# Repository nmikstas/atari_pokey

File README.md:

# atari_pokey
Recreation of the Atari POKEY chip (work in progress)

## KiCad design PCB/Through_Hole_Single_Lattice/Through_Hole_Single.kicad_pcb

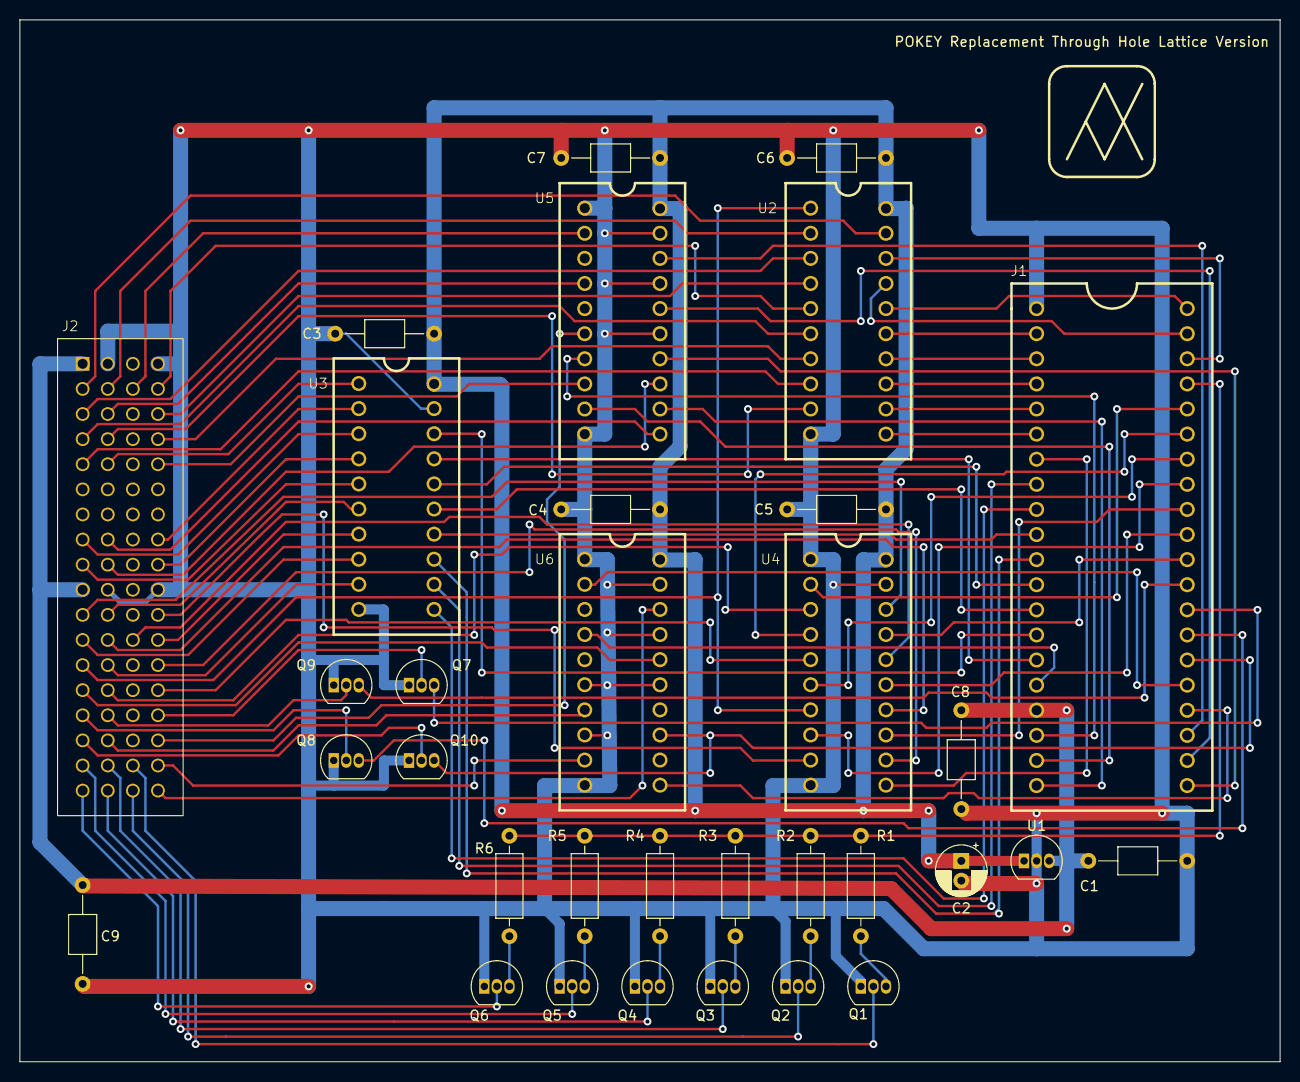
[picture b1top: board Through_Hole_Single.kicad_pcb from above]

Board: 2 copper layers, 127.5 x 105.4 mm, 33 parts (0 on the bottom side), 93 nets.

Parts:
C1, C3, C4, C5, C6, C7, C8, C9: .1uf; C_Axial_L3.8mm_D2.6mm_P10.00mm_Horizontal
C2: 10uf; CP_Radial_D5.0mm_P2.00mm
J1: 2x20_Conn; Con_2X20
J2: Proto-72Pin
Q1, Q2, Q3, Q4, Q5, Q6, Q7, Q8, Q9, Q10: TN2106; TO-92_Inline
R1: 825 1%; R_Axial_DIN0207_L6.3mm_D2.5mm_P10.16mm_Horizontal
R2: 1.65K 1%; R_Axial_DIN0207_L6.3mm_D2.5mm_P10.16mm_Horizontal
R3: 3.3K 1%; R_Axial_DIN0207_L6.3mm_D2.5mm_P10.16mm_Horizontal
R4: 7.68K 1%; R_Axial_DIN0207_L6.3mm_D2.5mm_P10.16mm_Horizontal
R5: 24K 1%; R_Axial_DIN0207_L6.3mm_D2.5mm_P10.16mm_Horizontal
R6: 75K 1%; R_Axial_DIN0207_L6.3mm_D2.5mm_P10.16mm_Horizontal
U1: L78L05_TO92; TO-92_Inline
U2, U3, U4, U5, U6: DIP_20

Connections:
+3.3V: C2.1, C3.1, C4.1, C5.1, C6.1, C7.1, U1.1 (VO), U2.20 (VCC), U3.20 (VCC), U4.20 (VCC), U5.20 (VCC), U6.20 (VCC)
+5V: C1.1, C8.1, C9.1, J1.17 (+5V), J2.1 (5V1), J2.37 (5V2), U1.3 (VI)
A0: J1.36 (A0), U4.2 (1A1)
A1: J1.35 (A1), U4.4 (1A2)
A2: J1.34 (A2), U4.6 (1A3)
A3: J1.33 (A3), U4.8 (1A4)
AUDIO: J1.37 (AUDIO), R1.1, R2.1, R3.1, R4.1, R5.1, R6.1
BCLK: J1.26 (BCLK), Q10.3 (D), U6.13 (2A2)
CS1: J1.31 (CS1), U4.15 (2A3)
D0: J1.38 (D0), U2.18 (B0)
D1: J1.39 (D1), U2.17 (B1)
D2: J1.40 (D2), U2.16 (B2)
D3: J1.2 (D3), U2.15 (B3)
D4: J1.3 (D4), U2.14 (B4)
D5: J1.4 (D5), U2.13 (B5)
D6: J1.5 (D6), U2.12 (B6)
D7: J1.6 (D7), U2.11 (B7)
GND: C1.2, C2.2, C3.2, C4.2, C5.2, C6.2, C7.2, C8.2, C9.2, J1.1 (GND), J2.2 (G1), J2.4 (G2), J2.38 (G3), J2.40 (G4), Q1.1 (S), Q2.1 (S), Q3.1 (S), Q4.1 (S), Q5.1 (S), Q6.1 (S), Q7.1 (S), Q8.1 (S), Q9.1 (S), Q10.1 (S), U1.2 (GND), U2.10 (GND), U3.10 (GND), U3.19 (CE), U4.1 (1~OE), U4.10 (GND), U4.19 (2~OE), U5.1 (1~OE), U5.10 (GND), U5.15 (2A3), U5.17 (2A4), U5.19 (2~OE), U6.1 (1~OE), U6.6 (1A3), U6.8 (1A4), U6.10 (GND), U6.15 (2A3), U6.17 (2A4), U6.19 (2~OE)
unnamed: Q1.3 (D), R1.2
unnamed: Q2.3 (D), R2.2
unnamed: Q3.3 (D), R3.2
unnamed: Q4.3 (D), R4.2
unnamed: Q5.3 (D), R5.2
unnamed: Q6.3 (D), R6.2
OCLK: J1.27 (OCLK), Q8.3 (D)
P0: J1.14 (P0), U3.18 (B0)
P1: J1.15 (P1), U3.17 (B1)
P2: J1.12 (P2), U3.16 (B2)
P3: J1.13 (P3), U3.15 (B3)
P4: J1.10 (P4), U3.14 (B4)
P5: J1.11 (P5), U3.13 (B5)
P6: J1.8 (P6), U3.12 (B6)
P7: J1.9 (P7), U3.11 (B7)
PHI2: J1.7 (PHI2), U4.11 (2A1)
R/W: J1.32 (R/W), U4.13 (2A2)
SID: J1.24 (SID), U6.11 (2A1)
SOD: J1.28 (SOD), Q7.3 (D)
_A0: J2.41 (B48), U4.18 (1Y1)
_A1: J2.47 (B6), U4.16 (1Y2)
_A2: J2.46 (B46), U4.14 (1Y3)
_A3: J2.52 (B8), U4.12 (1Y4)
_AUDIO0: J2.69 (B27), Q6.2 (G)
_AUDIO1: J2.65 (B30), Q5.2 (G)
_AUDIO2: J2.70 (B28), Q4.2 (G)
_AUDIO3: J2.66 (B31), Q3.2 (G)
_AUDIO4: J2.71 (B24), Q2.2 (G)
_AUDIO5: J2.67 (B21), Q1.2 (G)
_BCLKI: J2.62 (B34), U6.7 (2Y2)
_BCLKO: J2.61 (B33), Q10.2 (G)
_CS1: J2.56 (B11), U4.5 (2Y3)
_D0: J2.6 (A49), U2.2 (A0)
_D1: J2.9 (A45), U2.3 (A1)
_D2: J2.12 (A5), U2.4 (A2)
_D3: J2.8 (A2), U2.5 (A3)
_D4: J2.13 (A42), U2.6 (A4)
_D5: J2.16 (A8), U2.7 (A5)
_D6: J2.17 (A39), U2.8 (A6)
_D7: J2.14 (A43), U2.9 (A7)
_DUMP: J2.18 (A40), U3.1 (A->B)
_OCLK: J2.57 (B36), Q8.2 (G)
_P0: J2.32 (A20), U3.2 (A0)
_P1: J2.29 (A30), U3.3 (A1)
_P2: J2.36 (A23), U3.4 (A2)
_P3: J2.33 (A27), U3.5 (A3)
_P4: J2.42 (B49), U3.6 (A4)
_P5: J2.48 (B5), U3.7 (A5)
_P6: J2.45 (B45), U3.8 (A6)
_P7: J2.50 (B43), U3.9 (A7)
_PHI2: J2.44 (B2), U4.9 (2Y1)
_R/W: J2.49 (B42), U2.1 (A->B), U4.7 (2Y2)
_SID: J2.68 (B20), U6.9 (2Y1)
_SOD: J2.60 (B14), Q7.2 (G)
_~CS0: J2.54 (B40), U4.3 (2Y4)
_~IRQ: J2.58 (B37), Q9.2 (G)
_~K0: J2.7 (A3), U5.2 (1A1)
_~K1: J2.10 (A46), U5.4 (1A2)
_~K2: J2.64 (B17), U5.6 (1A3)
_~K3: J2.20 (A11), U5.8 (1A4)
_~K4: J2.30 (A31), U5.11 (2A1)
_~K5: J2.34 (A28), U5.13 (2A2)
_~KR1: J2.72 (B23), U6.18 (1Y1)
_~KR2: J2.53 (B39), U6.16 (1Y2)
~CS0: J1.30 (~CS0), U4.17 (2A4)
~IRQ: J1.29 (~IRQ), Q9.3 (D)
~K0: J1.23 (~K0), U5.18 (1Y1)
~K1: J1.22 (~K1), U5.16 (1Y2)
~K2: J1.21 (~K2), U5.14 (1Y3)
~K3: J1.20 (~K3), U5.12 (1Y4)
~K4: J1.19 (~K4), U5.9 (2Y1)
~K5: J1.18 (~K5), U5.7 (2Y2)
~KR1: J1.25 (~KR1), U6.2 (1A1)
~KR2: J1.16 (~KR2), U6.4 (1A2)
~_EN: J2.5 (A48), U2.19 (CE)

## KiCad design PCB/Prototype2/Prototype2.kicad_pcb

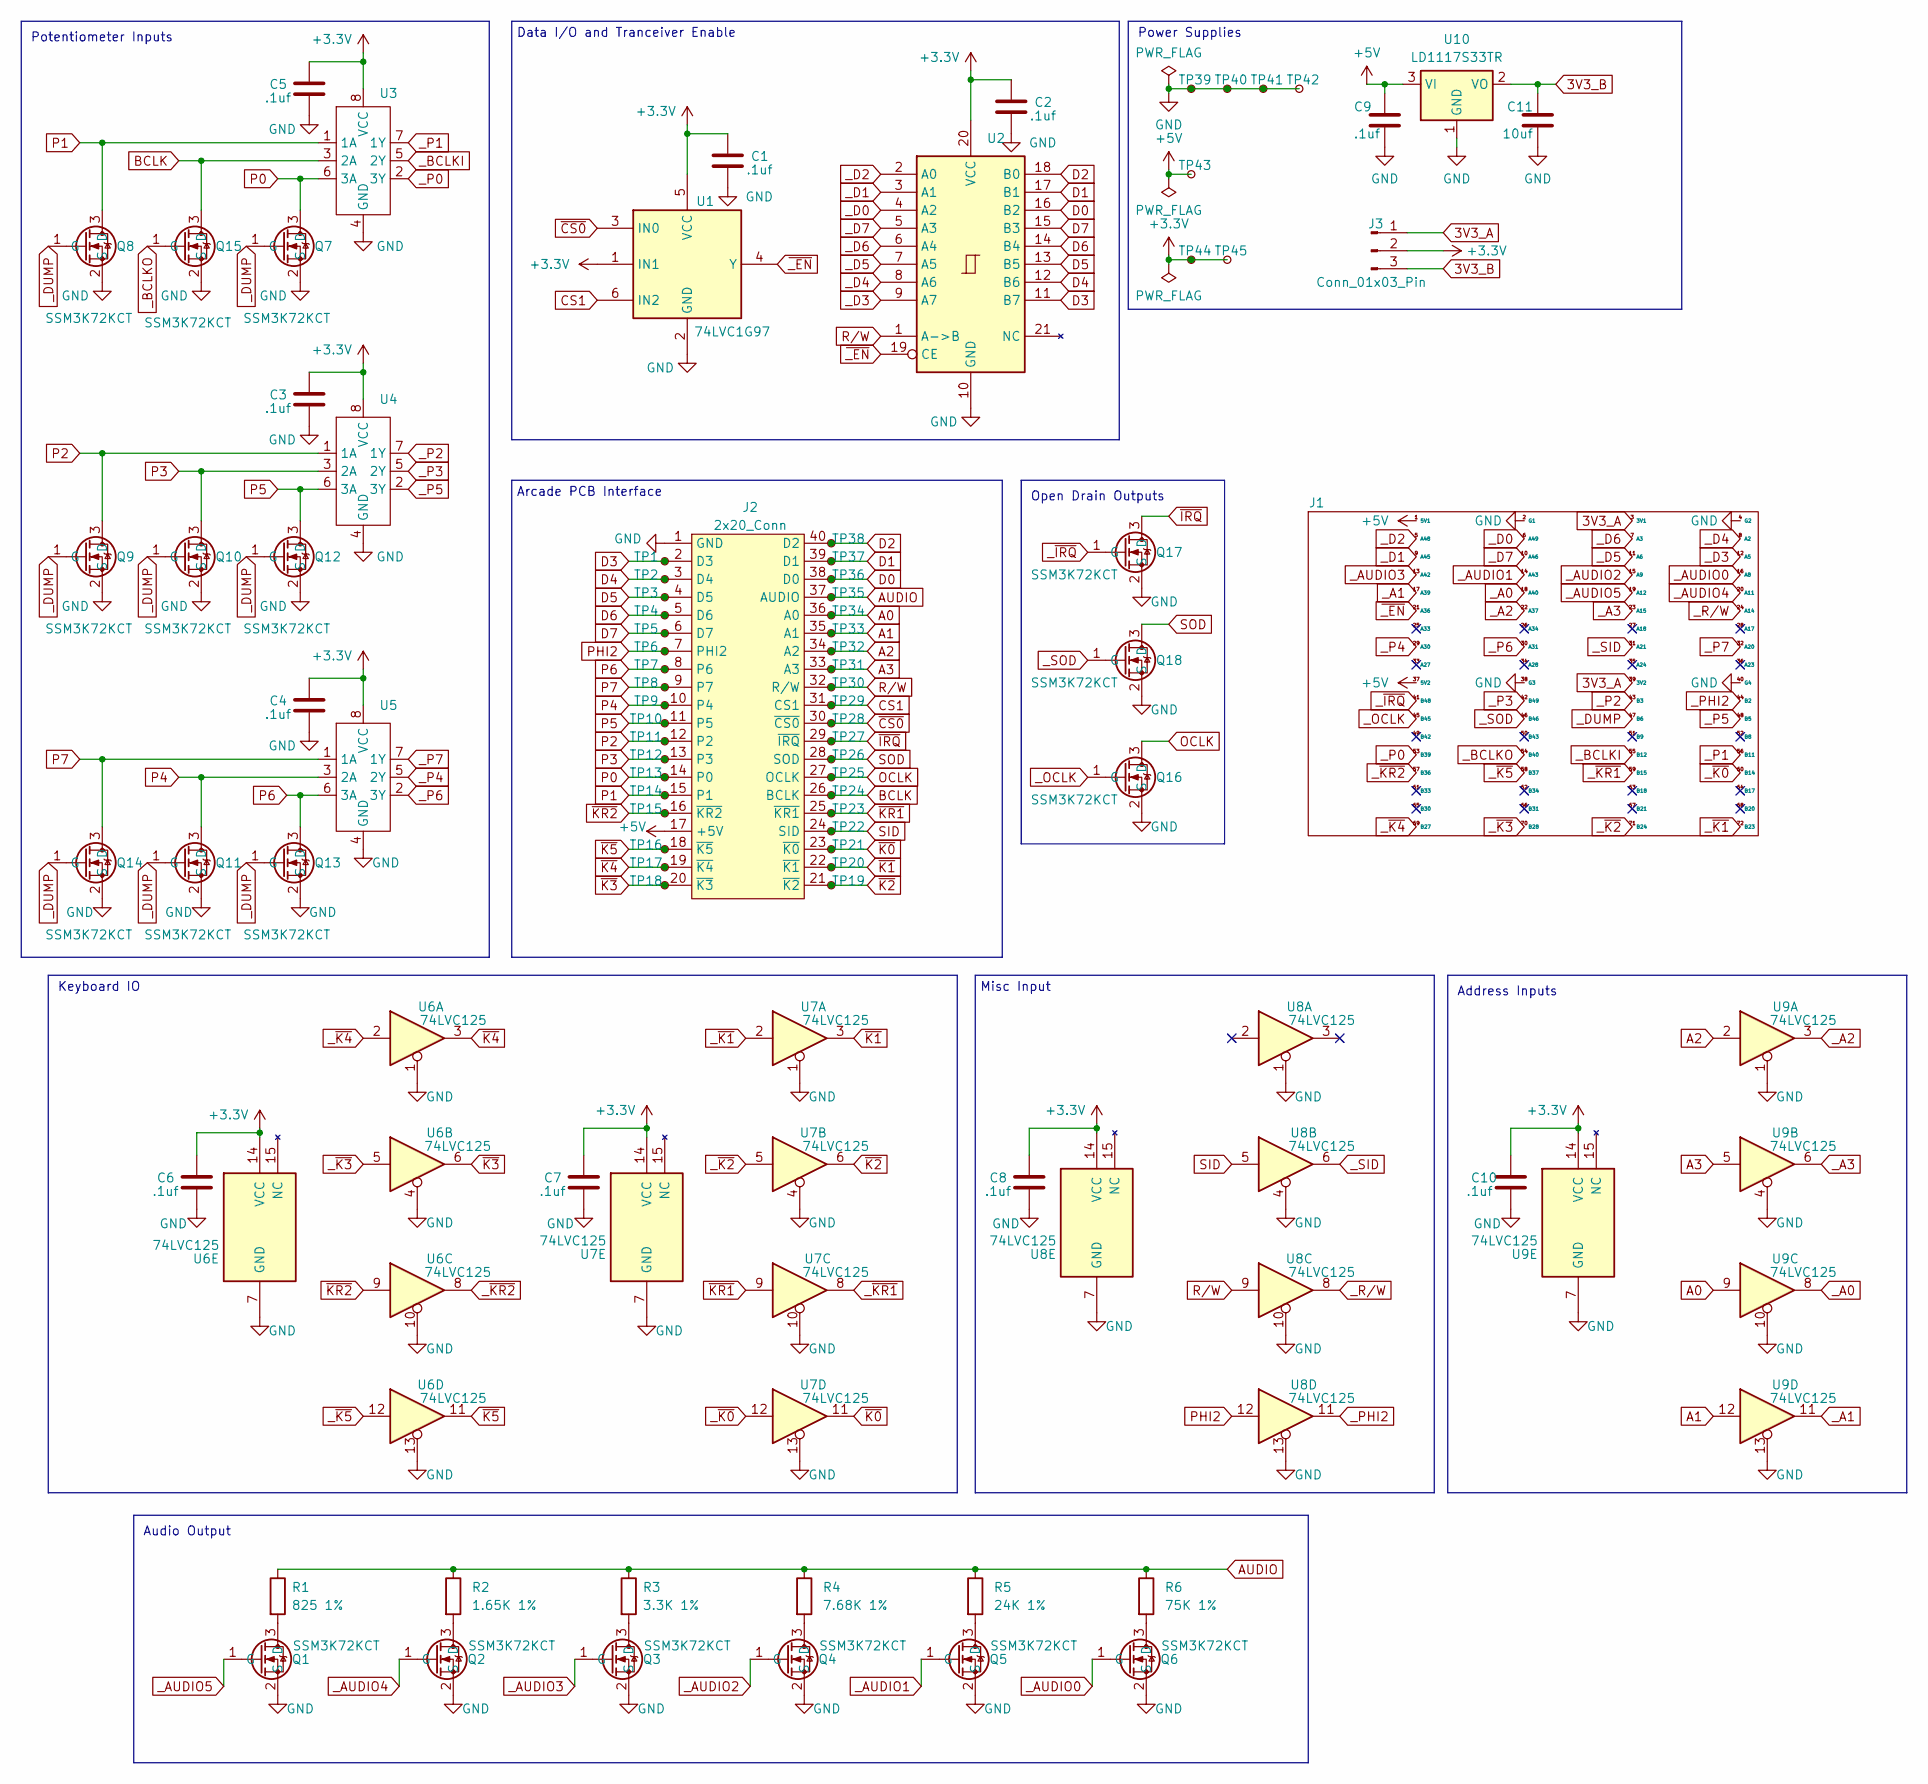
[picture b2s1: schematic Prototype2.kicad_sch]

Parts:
C1, C2, C3, C4, C5, C6, C7, C8, C9, C10: .1uf; C_0201_0603Metric
C11: 10uf; C_0805_2012Metric
J1: Proto-72Pin
J2: 2x20_Conn; Con_2X20
J3: Conn_01x03_Pin; PinSocket_1x03_P2.54mm_Vertical
Q1, Q2, Q3, Q4, Q5, Q6, Q7, Q8, Q9, Q10, Q11, Q12, Q13, Q14, Q15, Q16, Q17, Q18: SSM3K72KCT; CST3_TOS
R1: 825 1%; R_0402_1005Metric
R2: 1.65K 1%; R_0201_0603Metric
R3: 3.3K 1%; R_0201_0603Metric
R4: 7.68K 1%; R_0201_0603Metric
R5: 24K 1%; R_0201_0603Metric
R6: 75K 1%; R_0201_0603Metric
TP1, TP2, TP3, TP4, TP5, TP6, TP7, TP8, TP9, TP10, TP11, TP12, TP13, TP14, TP15, TP16, TP17, TP18, TP19, TP20, TP21, TP22, TP23, TP24, TP25, TP26, TP27, TP28, TP29, TP30, TP31, TP32, TP33, TP34, TP35, TP36, TP37, TP38, TP39, TP40, TP41, TP42, TP43, TP44, TP45: TP
U1: 74LVC1G97; DRY6
U2: VQFN20_RKS_TEX
U3, U4, U5: XSON8
U6, U7, U8, U9: 74LVC125; DHVQFN14_SOT762-1_NEX
U10: LD1117S33TR; Reg

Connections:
3V3_A: J1.3 (3V1), J1.39 (3V2), J3.1
3V3_B: C11.1, J3.3, U10.2 (VO)
+3.3V: C1.1, C2.1, C3.1, C4.1, C5.1, C6.1, C7.1, C8.1, C10.1, J3.2, TP44.1, TP45.1, U1.1 (IN1), U1.5 (VCC), U2.20 (VCC), U3.8 (VCC), U4.8 (VCC), U5.8 (VCC), U6.14 (VCC), U7.14 (VCC), U8.14 (VCC), U9.14 (VCC)
+5V: C9.1, J1.1 (5V1), J1.37 (5V2), J2.17 (+5V), TP43.1, U10.3 (VI)
A0: J2.36 (A0), TP34.1, U9.9
A1: J2.35 (A1), TP33.1, U9.12
A2: J2.34 (A2), TP32.1, U9.2
A3: J2.33 (A3), TP31.1, U9.5
AUDIO: J2.37 (AUDIO), R1.1, R2.1, R3.1, R4.1, R5.1, R6.1, TP35.1
BCLK: J2.26 (BCLK), Q15.3 (D), TP24.1, U3.3 (2A)
CS1: J2.31 (CS1), TP29.1, U1.6 (IN2)
D0: J2.38 (D0), TP36.1, U2.16 (B2)
D1: J2.39 (D1), TP37.1, U2.17 (B1)
D2: J2.40 (D2), TP38.1, U2.18 (B0)
D3: J2.2 (D3), TP1.1, U2.11 (B7)
D4: J2.3 (D4), TP2.1, U2.12 (B6)
D5: J2.4 (D5), TP3.1, U2.13 (B5)
D6: J2.5 (D6), TP4.1, U2.14 (B4)
D7: J2.6 (D7), TP5.1, U2.15 (B3)
GND: C1.2, C2.2, C3.2, C4.2, C5.2, C6.2, C7.2, C8.2, C9.2, C10.2, C11.2, J1.2 (G1), J1.4 (G2), J1.38 (G3), J1.40 (G4), J2.1 (GND), Q1.2 (S), Q2.2 (S), Q3.2 (S), Q4.2 (S), Q5.2 (S), Q6.2 (S), Q7.2 (S), Q8.2 (S), Q9.2 (S), Q10.2 (S), Q11.2 (S), Q12.2 (S), Q13.2 (S), Q14.2 (S), Q15.2 (S), Q16.2 (S), Q17.2 (S), Q18.2 (S), TP39.1, TP40.1, TP41.1, TP42.1, U1.2 (GND), U2.10 (GND), U3.4 (GND), U4.4 (GND), U5.4 (GND), U6.1, U6.4, U6.7 (GND), U6.10, U6.13, U7.1, U7.4, U7.7 (GND), U7.10, U7.13, U8.1, U8.4, U8.7 (GND), U8.10, U8.13, U9.1, U9.4, U9.7 (GND), U9.10, U9.13, U10.1 (GND)
unnamed: Q1.3 (D), R1.2
unnamed: Q2.3 (D), R2.2
unnamed: Q3.3 (D), R3.2
unnamed: Q4.3 (D), R4.2
unnamed: Q5.3 (D), R5.2
unnamed: Q6.3 (D), R6.2
OCLK: J2.27 (OCLK), Q16.3 (D), TP25.1
P0: J2.14 (P0), Q7.3 (D), TP13.1, U3.6 (3A)
P1: J2.15 (P1), Q8.3 (D), TP14.1, U3.1 (1A)
P2: J2.12 (P2), Q9.3 (D), TP11.1, U4.1 (1A)
P3: J2.13 (P3), Q10.3 (D), TP12.1, U4.3 (2A)
P4: J2.10 (P4), Q11.3 (D), TP9.1, U5.3 (2A)
P5: J2.11 (P5), Q12.3 (D), TP10.1, U4.6 (3A)
P6: J2.8 (P6), Q13.3 (D), TP7.1, U5.6 (3A)
P7: J2.9 (P7), Q14.3 (D), TP8.1, U5.1 (1A)
PHI2: J2.7 (PHI2), TP6.1, U8.12
R/W: J2.32 (R/W), TP30.1, U2.1 (A->B), U8.9
SID: J2.24 (SID), TP22.1, U8.5
SOD: J2.28 (SOD), Q18.3 (D), TP26.1
_A0: J1.18 (A40), U9.8
_A1: J1.17 (A39), U9.11
_A2: J1.22 (A37), U9.3
_A3: J1.23 (A15), U9.6
_AUDIO0: J1.16 (A8), Q6.1 (G)
_AUDIO1: J1.14 (A43), Q5.1 (G)
_AUDIO2: J1.15 (A9), Q4.1 (G)
_AUDIO3: J1.13 (A42), Q3.1 (G)
_AUDIO4: J1.20 (A11), Q2.1 (G)
_AUDIO5: J1.19 (A12), Q1.1 (G)
_BCLKI: J1.55 (B12), U3.5 (2Y)
_BCLKO: J1.54 (B40), Q15.1 (G)
_D0: J1.6 (A49), U2.4 (A2)
_D1: J1.9 (A45), U2.3 (A1)
_D2: J1.5 (A48), U2.2 (A0)
_D3: J1.12 (A5), U2.9 (A7)
_D4: J1.8 (A2), U2.8 (A6)
_D5: J1.11 (A6), U2.7 (A5)
_D6: J1.7 (A3), U2.6 (A4)
_D7: J1.10 (A46), U2.5 (A3)
_DUMP: J1.47 (B6), Q7.1 (G), Q8.1 (G), Q9.1 (G), Q10.1 (G), Q11.1 (G), Q12.1 (G), Q13.1 (G), Q14.1 (G)
_OCLK: J1.45 (B45), Q16.1 (G)
_P0: J1.53 (B39), U3.2 (3Y)
_P1: J1.56 (B11), U3.7 (1Y)
_P2: J1.43 (B3), U4.7 (1Y)
_P3: J1.42 (B49), U4.5 (2Y)
_P4: J1.29 (A30), U5.5 (2Y)
_P5: J1.48 (B5), U4.2 (3Y)
_P6: J1.30 (A31), U5.2 (3Y)
_P7: J1.32 (A20), U5.7 (1Y)
_PHI2: J1.44 (B2), U8.11
_R/W: J1.24 (A14), U8.8
_SID: J1.31 (A21), U8.6
_SOD: J1.46 (B46), Q18.1 (G)
_~IRQ: J1.41 (B48), Q17.1 (G)
_~K0: J1.60 (B14), U7.12
_~K1: J1.72 (B23), U7.2
_~K2: J1.71 (B24), U7.5
_~K3: J1.70 (B28), U6.5
_~K4: J1.69 (B27), U6.2
_~K5: J1.58 (B37), U6.12
_~KR1: J1.59 (B15), U7.8
_~KR2: J1.57 (B36), U6.8
~CS0: J2.30 (~CS0), TP28.1, U1.3 (IN0)
~IRQ: J2.29 (~IRQ), Q17.3 (D), TP27.1
~K0: J2.23 (~K0), TP21.1, U7.11
~K1: J2.22 (~K1), TP20.1, U7.3
~K2: J2.21 (~K2), TP19.1, U7.6
~K3: J2.20 (~K3), TP18.1, U6.6
~K4: J2.19 (~K4), TP17.1, U6.3
~K5: J2.18 (~K5), TP16.1, U6.11
~KR1: J2.25 (~KR1), TP23.1, U7.9
~KR2: J2.16 (~KR2), TP15.1, U6.9
~_EN: J1.21 (A36), U1.4 (Y), U2.19 (CE)

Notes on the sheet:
Keyboard IO
Power Supplies
Potentiometer Inputs
Arcade PCB Interface
Data I/O and Tranceiver Enable
Audio Output
Address Inputs
Misc Input
Open Drain Outputs

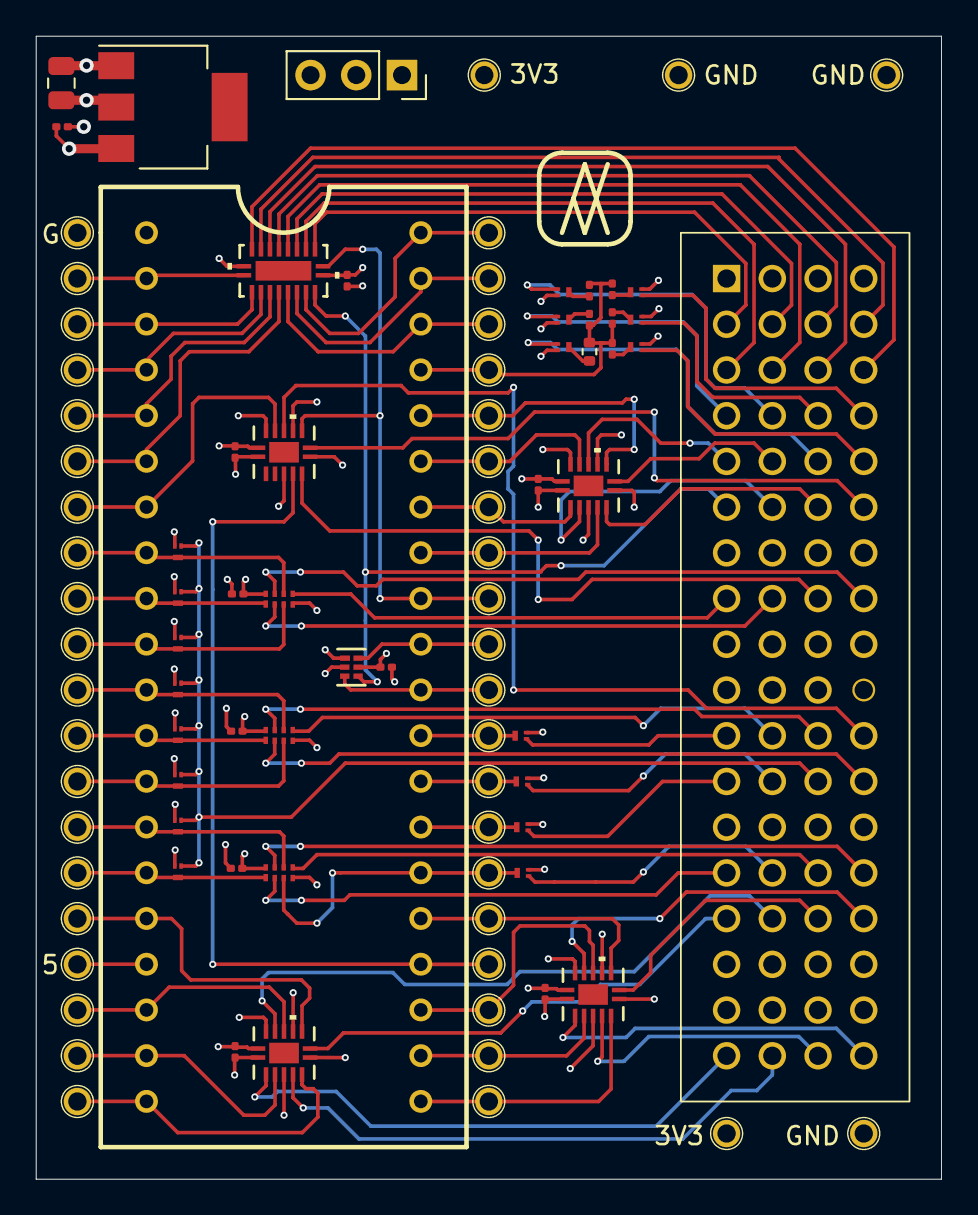
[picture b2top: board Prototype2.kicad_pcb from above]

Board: 4 copper layers, 50.3 x 63.5 mm, 93 parts (0 on the bottom side), 93 nets.

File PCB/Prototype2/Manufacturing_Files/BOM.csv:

Quantity           Component                                                   Value               Part#
10                 C1 C2 C3 C4 C5 C6 C7 C8 C9 C10                              .1uf                Digikey 1292-1161-1-ND or equivalent
1                  C11                                                         10uf                Digikey 1276-1096-1-ND or equivalent
1                  J1                                                          4X18_Conn           N/A
1                  J2                                                          2x20_Conn           N/A
1                  J3                                                          1x03_Pin            N/A

18                 Q1  Q2  Q3  Q4  Q5  Q6  Q7  Q8  Q9  Q10                     SSM3K72KCT          Digikey SSM3K72KCTL3FCT-ND or equivalent
                   Q11 Q12 Q13 Q14 Q15 Q16 Q17 Q18

1                  R1                                                          825 1%              Digikey YAG3242CT-ND or equivalent
1                  R2                                                          1.65K 1%            Digikey YAG2486CT-ND or equivalent
1                  R3                                                          3.3K 1%             Digikey YAG2285CT-ND or equivalent
1                  R4                                                          7.68K 1%            Digikey YAG2806CT-ND or equivalent
1                  R5                                                          24K 1%              Digikey YAG2336CT-ND or equivalent
1                  R6                                                          75K 1%              Digikey YAG2795CT-ND or equivalent

46                 TP1  TP2  TP3  TP4  TP5  TP6  TP7  TP8  TP9  TP10           Test point          N/A
                   TP11 TP12 TP13 TP14 TP15 TP16 TP17 TP18 TP19 TP20
                   TP21 TP22 TP23 TP24 TP25 TP26 TP27 TP28 TP29 TP30
                   TP31 TP32 TP33 TP34 TP35 TP36 TP37 TP38 TP39 TP40
                   TP41 TP42 TP43 TP44 TP45 TP46

1                  U1                                                          74LVC1G97           296-29874-1-ND or equivalent
1                  U2                                                          74LVC245            1727-3495-1-ND or equivalent
3                  U3 U4 U5                                                    74LVC3G14           1727-7042-1-ND or equivalent
4                  U6 U7 U8 U9                                                 74LVC125            1727-3481-1-ND or equivalent
1                  U10                                                         LD1117S33TR         497-1242-1-ND  or equivalent

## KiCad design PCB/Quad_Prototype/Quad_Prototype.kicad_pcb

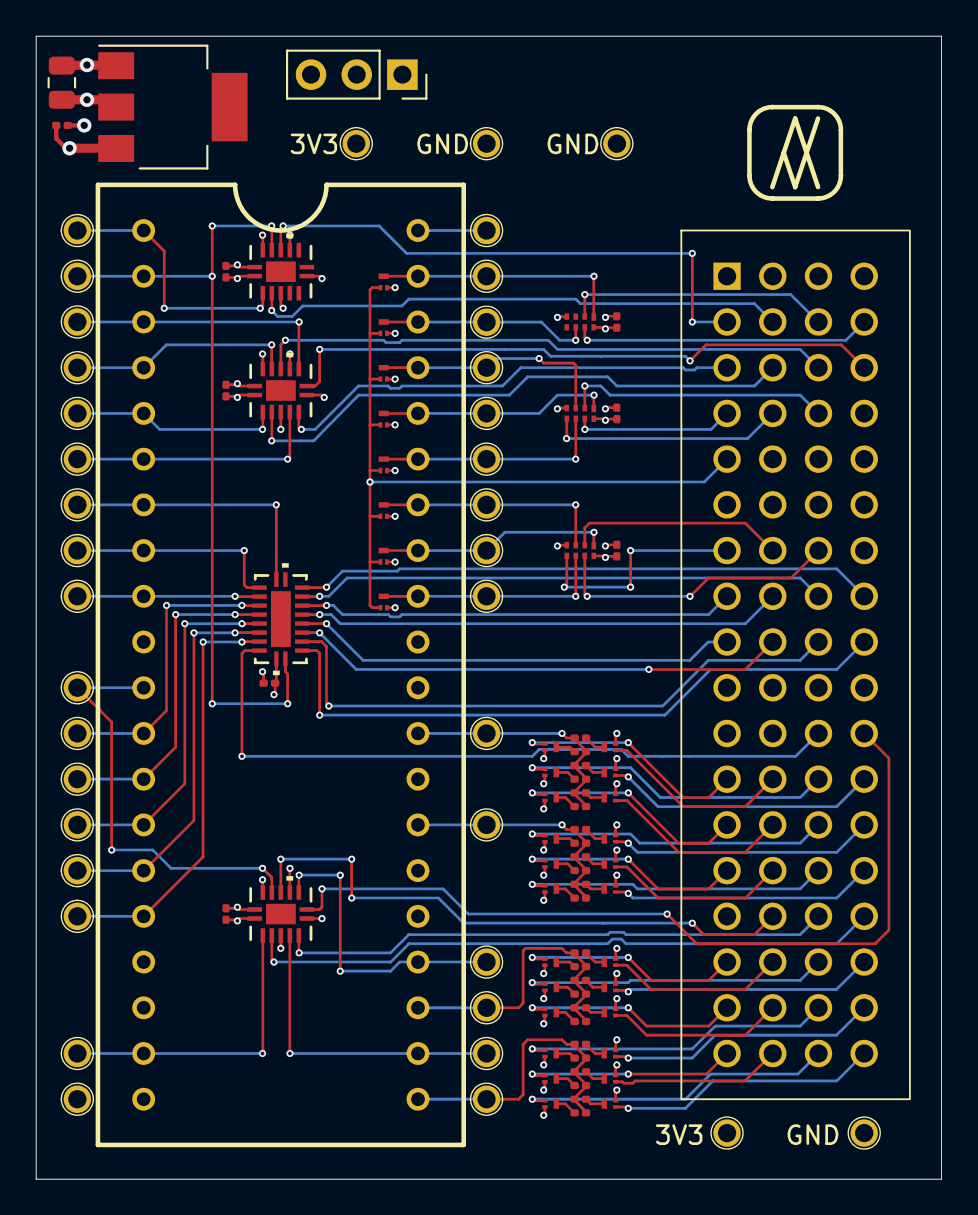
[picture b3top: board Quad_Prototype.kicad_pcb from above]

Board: 4 copper layers, 50.3 x 63.5 mm, 113 parts (0 on the bottom side), 111 nets.

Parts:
C1, C3, C4, C5, C6, C7, C8, C9: .1uf; C_0201_0603Metric
C2: 10uf; C_0805_2012Metric
J1: Con_2X20
J2: Proto-72Pin
J3: Conn_01x03_Pin; PinSocket_1x03_P2.54mm_Vertical
Q1, Q2, Q3, Q4, Q5, Q6, Q7, Q8, Q9, Q10, Q11, Q12, Q13, Q14, Q15, Q16, Q17, Q18, Q19, Q20, Q21, Q22, Q23, Q24, Q25, Q26, Q27, Q29, Q30, Q31, Q32, Q33: SSM3K72KCT; CST3_TOS
R1, R7, R13, R19: 825 1%; R_0201_0603Metric
R2, R8, R14, R20: 1.65K 1%; R_0201_0603Metric
R3, R9, R15, R21: 3.3K 1%; R_0201_0603Metric
R4, R10, R16, R22: 7.68K 1%; R_0201_0603Metric
R5, R11, R17, R23: 24K 1%; R_0201_0603Metric
R6, R12, R18, R24: 75K 1%; R_0201_0603Metric
TP1, TP2, TP3, TP4, TP5, TP6, TP7, TP8, TP9, TP10, TP11, TP12, TP13, TP14, TP15, TP16, TP17, TP18, TP19, TP20, TP21, TP22, TP23, TP24, TP25, TP26, TP27, TP28, TP29, TP30, TP31, TP32, TP33, TP34, TP35, TP36, TP37: TP
U1: LD1117S33TR; Reg
U2: VQFN20_RKS_TEX
U3, U7, U8: 74LVC125; DHVQFN14_SOT762-1_NEX
U4, U5, U6: XSON8

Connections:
3V3_A: J2.3 (3V1), J2.39 (3V2), J3.1
3V3_B: C2.1, J3.3, U1.2 (VO)
+3.3V: C3.1, C4.1, C5.1, C6.1, C7.1, C8.1, C9.1, J3.2, TP3.1, TP5.1, U2.20 (VCC), U3.14 (VCC), U4.8 (VCC), U5.8 (VCC), U6.8 (VCC), U7.14 (VCC), U8.14 (VCC)
+5V: C1.1, J1.40 (VCC), J2.1 (5V1), J2.37 (5V2), TP2.1, U1.3 (VI)
A0: J1.6 (A0), TP13.1, U3.5
A1: J1.5 (A1), TP12.1, U3.2
A2: J1.4 (A2), TP11.1, U3.12
A3: J1.3 (A3), TP10.1, U3.9
AUDIO1: J1.23 (OUT1), R1.1, R2.1, R3.1, R4.1, R5.1, R6.1, TP26.1
AUDIO2: J1.29 (OUT2), R7.1, R8.1, R9.1, R10.1, R11.1, R12.1, TP29.1
AUDIO3: J1.27 (OUT3), R13.1, R14.1, R15.1, R16.1, R17.1, R18.1, TP28.1
AUDIO4: J1.21 (OUT4), R19.1, R20.1, R21.1, R22.1, R23.1, R24.1, TP24.1
D0: J1.7 (D0), TP14.1, U2.11 (B7)
D1: J1.8 (D1), TP15.1, U2.12 (B6)
D2: J1.9 (D2), TP16.1, U2.13 (B5)
D3: J1.12 (D3), TP18.1, U2.14 (B4)
D4: J1.13 (D4), TP19.1, U2.15 (B3)
D5: J1.14 (D5), TP20.1, U2.16 (B2)
D6: J1.15 (D6), TP21.1, U2.17 (B1)
D7: J1.16 (D7), TP22.1, U2.18 (B0)
GND: C1.2, C2.2, C3.2, C4.2, C5.2, C6.2, C7.2, C8.2, C9.2, J1.20 (GND), J2.2 (G1), J2.4 (G2), J2.38 (G3), J2.40 (G4), Q1.2 (S), Q2.2 (S), Q3.2 (S), Q4.2 (S), Q5.2 (S), Q6.2 (S), Q7.2 (S), Q8.2 (S), Q9.2 (S), Q10.2 (S), Q11.2 (S), Q12.2 (S), Q13.2 (S), Q14.2 (S), Q15.2 (S), Q16.2 (S), Q17.2 (S), Q18.2 (S), Q19.2 (S), Q20.2 (S), Q21.2 (S), Q22.2 (S), Q23.2 (S), Q24.2 (S), Q25.2 (S), Q26.2 (S), Q27.2 (S), Q29.2 (S), Q30.2 (S), Q31.2 (S), Q32.2 (S), Q33.2 (S), TP1.1, TP4.1, TP6.1, TP7.1, U1.1 (GND), U2.10 (GND), U3.1, U3.4, U3.7 (GND), U3.10, U3.13, U4.4 (GND), U5.4 (GND), U6.4 (GND), U7.1, U7.4, U7.7 (GND), U7.10, U7.13, U8.1, U8.4, U8.7 (GND), U8.10, U8.13
unnamed: Q1.3 (D), R1.2
unnamed: Q2.3 (D), R2.2
unnamed: Q3.3 (D), R3.2
unnamed: Q4.3 (D), R4.2
unnamed: Q5.3 (D), R5.2
unnamed: Q6.3 (D), R6.2
unnamed: Q7.3 (D), R7.2
unnamed: Q8.3 (D), R8.2
unnamed: Q9.3 (D), R9.2
unnamed: Q10.3 (D), R10.2
unnamed: Q11.3 (D), R11.2
unnamed: Q12.3 (D), R12.2
unnamed: Q13.3 (D), R13.2
unnamed: Q14.3 (D), R14.2
unnamed: Q15.3 (D), R15.2
unnamed: Q16.3 (D), R16.2
unnamed: Q17.3 (D), R17.2
unnamed: Q18.3 (D), R18.2
unnamed: Q19.3 (D), R19.2
unnamed: Q20.3 (D), R20.2
unnamed: Q21.3 (D), R21.2
unnamed: Q22.3 (D), R22.2
unnamed: Q23.3 (D), R23.2
unnamed: Q24.3 (D), R24.2
P0: J1.38 (P1_0), Q31.3 (D), TP36.1, U4.6 (3A)
P1: J1.39 (P1_1), Q25.3 (D), TP37.1, U4.1 (1A)
P2: J1.36 (P1_2), Q26.3 (D), TP34.1, U5.1 (1A)
P3: J1.37 (P1_3), Q29.3 (D), TP35.1, U5.3 (2A)
P4: J1.34 (P1_4), Q30.3 (D), TP32.1, U6.3 (2A)
P5: J1.35 (P1_5), Q32.3 (D), TP33.1, U5.6 (3A)
P6: J1.32 (P1_6), Q33.3 (D), TP30.1, U6.6 (3A)
P7: J1.33 (P1_7), Q27.3 (D), TP31.1, U6.1 (1A)
PHI2: J1.24 (PHI2), TP27.1, U8.9
R/W: J1.2 (R/W), TP9.1, U2.1 (A->B), U7.12
_A0: J2.9 (A45), U3.6
_A1: J2.10 (A46), U3.3
_A2: J2.11 (A6), U3.11
_A3: J2.12 (A5), U3.8
_AUDIO1_0: J2.61 (B33), Q6.1 (G)
_AUDIO1_1: J2.62 (B34), Q5.1 (G)
_AUDIO1_2: J2.63 (B18), Q4.1 (G)
_AUDIO1_3: J2.64 (B17), Q3.1 (G)
_AUDIO1_4: J2.65 (B30), Q2.1 (G)
_AUDIO1_5: J2.66 (B31), Q1.1 (G)
_AUDIO2_0: J2.45 (B45), Q12.1 (G)
_AUDIO2_1: J2.46 (B46), Q11.1 (G)
_AUDIO2_2: J2.47 (B6), Q10.1 (G)
_AUDIO2_3: J2.48 (B5), Q9.1 (G)
_AUDIO2_4: J2.49 (B42), Q8.1 (G)
_AUDIO2_5: J2.50 (B43), Q7.1 (G)
_AUDIO3_0: J2.51 (B9), Q18.1 (G)
_AUDIO3_1: J2.52 (B8), Q17.1 (G)
_AUDIO3_2: J2.53 (B39), Q16.1 (G)
_AUDIO3_3: J2.54 (B40), Q15.1 (G)
_AUDIO3_4: J2.55 (B12), Q14.1 (G)
_AUDIO3_5: J2.56 (B11), Q13.1 (G)
_AUDIO4_0: J2.67 (B21), Q24.1 (G)
_AUDIO4_1: J2.68 (B20), Q23.1 (G)
_AUDIO4_2: J2.69 (B27), Q22.1 (G)
_AUDIO4_3: J2.70 (B28), Q21.1 (G)
_AUDIO4_4: J2.71 (B24), Q20.1 (G)
_AUDIO4_5: J2.72 (B23), Q19.1 (G)
_D0: J2.32 (A20), U2.9 (A7)
_D1: J2.31 (A21), U2.8 (A6)
_D2: J2.29 (A30), U2.7 (A5)
_D3: J2.30 (A31), U2.6 (A4)
_D4: J2.33 (A27), U2.5 (A3)
_D5: J2.34 (A28), U2.4 (A2)
_D6: J2.35 (A24), U2.3 (A1)
_D7: J2.36 (A23), U2.2 (A0)
_DUMP: J2.17 (A39), Q25.1 (G), Q26.1 (G), Q27.1 (G), Q29.1 (G), Q30.1 (G), Q31.1 (G), Q32.1 (G), Q33.1 (G)
_P0: J2.7 (A3), U4.2 (3Y)
_P1: J2.8 (A2), U4.7 (1Y)
_P2: J2.13 (A42), U5.7 (1Y)
_P3: J2.14 (A43), U5.5 (2Y)
_P4: J2.25 (A33), U6.5 (2Y)
_P5: J2.15 (A9), U5.2 (3Y)
_P6: J2.26 (A34), U6.2 (3Y)
_P7: J2.27 (A18), U6.7 (1Y)
_PHI2: J2.44 (B2), U8.8
_R/W: J2.5 (A48), U7.11
~CS1: J1.1 (~CS1), TP8.1, U7.2
~CS2: J1.22 (~CS2), TP25.1, U8.5
~CS3: J1.11 (~CS3), TP17.1, U8.12
~CS4: J1.19 (~CS4), TP23.1, U8.2
~_CS1: J2.6 (A49), U7.3
~_CS2: J2.59 (B15), U8.6
~_CS3: J2.58 (B37), U8.11
~_CS4: J2.60 (B14), U8.3
~_EN: J2.43 (B3), U2.19 (CE)

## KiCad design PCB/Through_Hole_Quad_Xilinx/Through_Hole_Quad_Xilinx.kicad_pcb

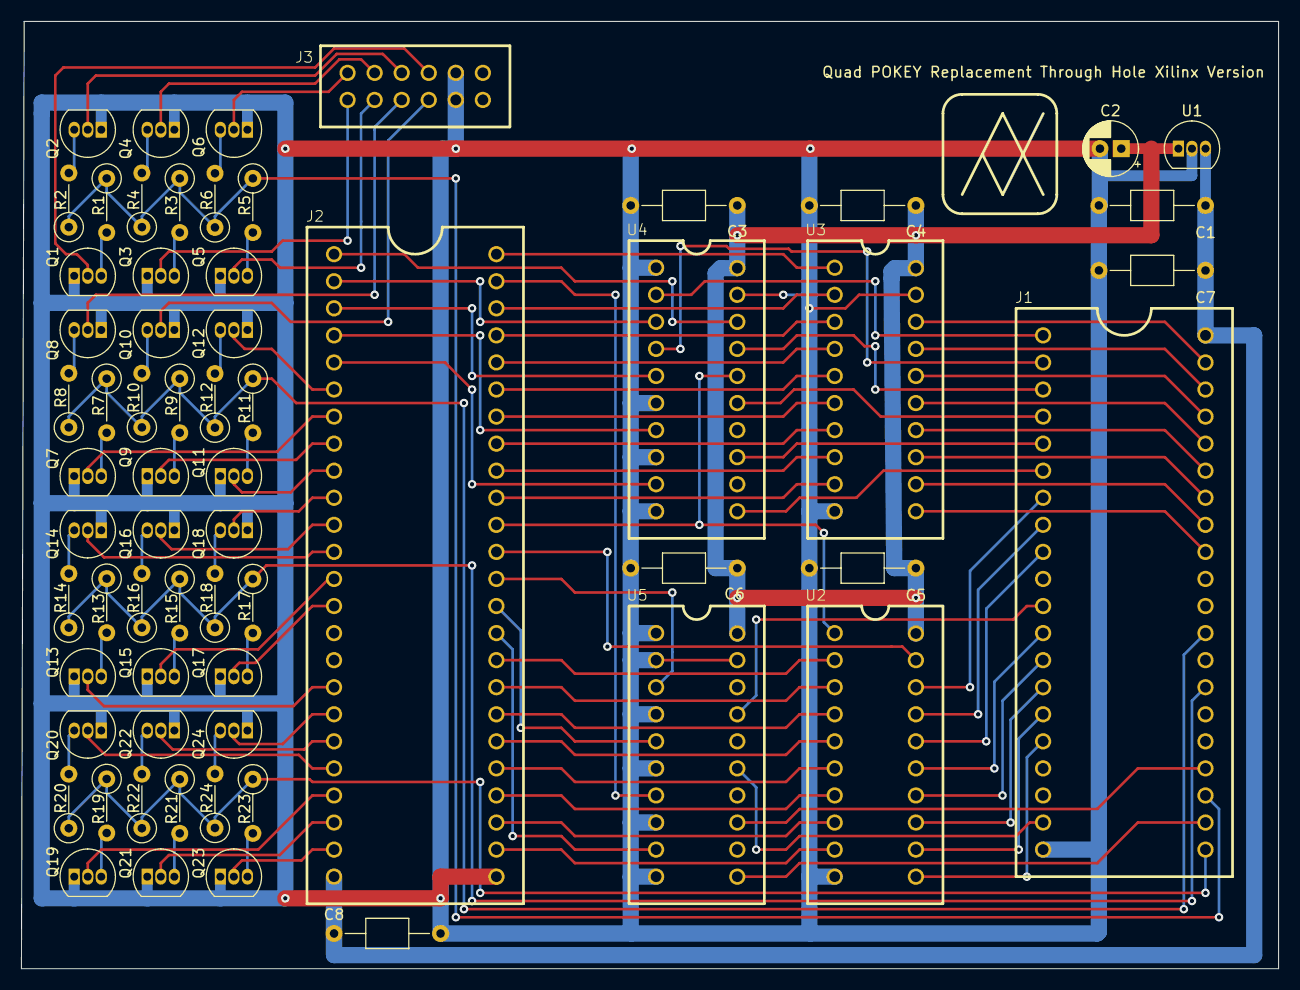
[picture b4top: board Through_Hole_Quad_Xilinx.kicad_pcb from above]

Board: 2 copper layers, 118.0 x 88.9 mm, 64 parts (0 on the bottom side), 109 nets.

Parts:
C1, C3, C4, C5, C6, C7, C8: .1uf; C_Axial_L3.8mm_D2.6mm_P10.00mm_Horizontal
C2: 10uf; CP_Radial_D5.0mm_P2.00mm
J1: Con_2X20
J2: CMOD-A7; Con_2X24
J3: PMOD
Q1, Q2, Q3, Q4, Q5, Q6, Q7, Q8, Q9, Q10, Q11, Q12, Q13, Q14, Q15, Q16, Q17, Q18, Q19, Q20, Q21, Q22, Q23, Q24: TN2106; TO-92_Inline
R1, R7, R13, R19: 825 1%; R_Axial_DIN0207_L6.3mm_D2.5mm_P5.08mm_Vertical
R2, R8, R14, R20: 1.65K 1%; R_Axial_DIN0207_L6.3mm_D2.5mm_P5.08mm_Vertical
R3, R9, R15, R21: 3.3K 1%; R_Axial_DIN0207_L6.3mm_D2.5mm_P5.08mm_Vertical
R4, R10, R16, R22: 7.68K 1%; R_Axial_DIN0207_L6.3mm_D2.5mm_P5.08mm_Vertical
R5, R11, R17, R23: 24K 1%; R_Axial_DIN0207_L6.3mm_D2.5mm_P5.08mm_Vertical
R6, R12, R18, R24: 75K 1%; R_Axial_DIN0207_L6.3mm_D2.5mm_P5.08mm_Vertical
U1: L78L05_TO92; TO-92_Inline
U2, U3, U4, U5: DIP_20

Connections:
+3.3V: C2.1, C3.1, C4.1, C5.1, C6.1, U1.1 (VO), U2.20 (VCC), U3.20 (VCC), U4.20 (VCC), U5.20 (VCC)
+5V: C1.1, C7.1, C8.1, J1.40 (VCC), J2.24 (VU), U1.3 (VI)
A0: J1.6 (A0), U4.11 (2A1)
A1: J1.5 (A1), U4.13 (2A2)
A2: J1.4 (A2), U4.15 (2A3)
A3: J1.3 (A3), U4.17 (2A4)
AUDIO1: J1.23 (OUT1), R1.1, R2.1, R3.1, R4.1, R5.1, R6.1
AUDIO2: J1.29 (OUT2), R7.1, R8.1, R9.1, R10.1, R11.1, R12.1
AUDIO3: J1.27 (OUT3), R13.1, R14.1, R15.1, R16.1, R17.1, R18.1
AUDIO4: J1.21 (OUT4), R19.1, R20.1, R21.1, R22.1, R23.1, R24.1
D0: J1.7 (D0), U2.18 (B0)
D1: J1.8 (D1), U2.17 (B1)
D2: J1.9 (D2), U2.16 (B2)
D3: J1.12 (D3), U2.15 (B3)
D4: J1.13 (D4), U2.14 (B4)
D5: J1.14 (D5), U2.13 (B5)
D6: J1.15 (D6), U2.12 (B6)
D7: J1.16 (D7), U2.11 (B7)
GND: C1.2, C2.2, C3.2, C4.2, C5.2, C6.2, C7.2, C8.2, J1.20 (GND), J2.25 (GND), J3.5 (G), J3.11 (G), Q1.1 (S), Q2.1 (S), Q3.1 (S), Q4.1 (S), Q5.1 (S), Q6.1 (S), Q7.1 (S), Q8.1 (S), Q9.1 (S), Q10.1 (S), Q11.1 (S), Q12.1 (S), Q13.1 (S), Q14.1 (S), Q15.1 (S), Q16.1 (S), Q17.1 (S), Q18.1 (S), Q19.1 (S), Q20.1 (S), Q21.1 (S), Q22.1 (S), Q23.1 (S), Q24.1 (S), U1.2 (GND), U2.10 (GND), U3.10 (GND), U3.19 (CE), U4.1 (1~OE), U4.6 (1A3), U4.8 (1A4), U4.10 (GND), U4.19 (2~OE), U5.1 (1~OE), U5.2 (1A1), U5.4 (1A2), U5.6 (1A3), U5.8 (1A4), U5.10 (GND), U5.19 (2~OE)
unnamed: Q1.3 (D), R1.2
unnamed: Q2.3 (D), R2.2
unnamed: Q3.3 (D), R3.2
unnamed: Q4.3 (D), R4.2
unnamed: Q5.3 (D), R5.2
unnamed: Q6.3 (D), R6.2
unnamed: Q7.3 (D), R7.2
unnamed: Q8.3 (D), R8.2
unnamed: Q9.3 (D), R9.2
unnamed: Q10.3 (D), R10.2
unnamed: Q11.3 (D), R11.2
unnamed: Q12.3 (D), R12.2
unnamed: Q13.3 (D), R13.2
unnamed: Q14.3 (D), R14.2
unnamed: Q15.3 (D), R15.2
unnamed: Q16.3 (D), R16.2
unnamed: Q17.3 (D), R17.2
unnamed: Q18.3 (D), R18.2
unnamed: Q19.3 (D), R19.2
unnamed: Q20.3 (D), R20.2
unnamed: Q21.3 (D), R21.2
unnamed: Q22.3 (D), R22.2
unnamed: Q23.3 (D), R23.2
unnamed: Q24.3 (D), R24.2
P0: J1.38 (P1_0), U3.17 (B1)
P1: J1.39 (P1_1), U3.18 (B0)
P2: J1.36 (P1_2), U3.15 (B3)
P3: J1.37 (P1_3), U3.16 (B2)
P4: J1.34 (P1_4), U3.13 (B5)
P5: J1.35 (P1_5), U3.14 (B4)
P6: J1.32 (P1_6), U3.11 (B7)
P7: J1.33 (P1_7), U3.12 (B6)
PHI2: J1.24 (PHI2), U5.13 (2A2)
R/W: J1.2 (R/W), U4.4 (1A2)
_A0: J2.5 (PIO05), U4.9 (2Y1)
_A1: J2.4 (PIO04), U4.7 (2Y2)
_A2: J2.3 (PIO03), U4.5 (2Y3)
_A3: J2.2 (PIO02), U4.3 (2Y4)
_AUDIO1_0: J3.7 (JA7), Q6.2 (G)
_AUDIO1_1: J3.2 (JA2), Q5.2 (G)
_AUDIO1_2: J3.8 (JA8), Q4.2 (G)
_AUDIO1_3: J3.1 (JA1), Q3.2 (G)
_AUDIO1_4: J3.9 (JA9), Q2.2 (G)
_AUDIO1_5: J3.10 (JA10), Q1.2 (G)
_AUDIO2_0: J2.6 (PIO06), Q12.2 (G)
_AUDIO2_1: J2.9 (PIO09), Q11.2 (G)
_AUDIO2_2: J3.4 (JA4), Q10.2 (G)
_AUDIO2_3: J2.8 (PIO08), Q9.2 (G)
_AUDIO2_4: J3.3 (JA3), Q8.2 (G)
_AUDIO2_5: J2.7 (PIO07), Q7.2 (G)
_AUDIO3_0: J2.10 (PIO10), Q18.2 (G)
_AUDIO3_1: J2.14 (PIO14), Q17.2 (G)
_AUDIO3_2: J2.11 (PIO11), Q16.2 (G)
_AUDIO3_3: J2.13 (PIO13), Q15.2 (G)
_AUDIO3_4: J2.12 (PIO12), Q14.2 (G)
_AUDIO3_5: J2.17 (PIO17), Q13.2 (G)
_AUDIO4_0: J2.18 (PIO18), Q24.2 (G)
_AUDIO4_1: J2.23 (PIO23), Q23.2 (G)
_AUDIO4_2: J2.19 (PIO19), Q22.2 (G)
_AUDIO4_3: J2.22 (PIO22), Q21.2 (G)
_AUDIO4_4: J2.20 (PIO20), Q20.2 (G)
_AUDIO4_5: J2.21 (PIO21), Q19.2 (G)
_D0: J2.33 (PIO33), U2.2 (A0)
_D1: J2.32 (PIO32), U2.3 (A1)
_D2: J2.31 (PIO31), U2.4 (A2)
_D3: J2.30 (PIO30), U2.5 (A3)
_D4: J2.29 (PIO29), U2.6 (A4)
_D5: J2.28 (PIO28), U2.7 (A5)
_D6: J2.27 (PIO27), U2.8 (A6)
_D7: J2.26 (PIO26), U2.9 (A7)
_DUMP: J2.48 (PIO48), U3.1 (A->B)
_P0: J2.45 (PIO45), U3.3 (A1)
_P1: J2.46 (PIO46), U3.2 (A0)
_P2: J2.43 (PIO43), U3.5 (A3)
_P3: J2.44 (PIO44), U3.4 (A2)
_P4: J2.41 (PIO41), U3.7 (A5)
_P5: J2.42 (PIO42), U3.6 (A4)
_P6: J2.39 (PIO39), U3.9 (A7)
_P7: J2.40 (PIO40), U3.8 (A6)
_PHI2: J2.47 (PIO47), U5.7 (2Y2)
_R/W: J2.38 (PIO38), U2.1 (A->B), U4.16 (1Y2)
_~CS1: J2.1 (PIO01), U4.18 (1Y1)
_~CS2: J2.34 (PIO34), U5.9 (2Y1)
_~CS3: J2.36 (PIO36), U5.3 (2Y4)
_~CS4: J2.35 (PIO35), U5.5 (2Y3)
~CS1: J1.1 (~CS1), U4.2 (1A1)
~CS2: J1.22 (~CS2), U5.11 (2A1)
~CS3: J1.11 (~CS3), U5.17 (2A4)
~CS4: J1.19 (~CS4), U5.15 (2A3)
~_EN: J2.37 (PIO37), U2.19 (CE)
